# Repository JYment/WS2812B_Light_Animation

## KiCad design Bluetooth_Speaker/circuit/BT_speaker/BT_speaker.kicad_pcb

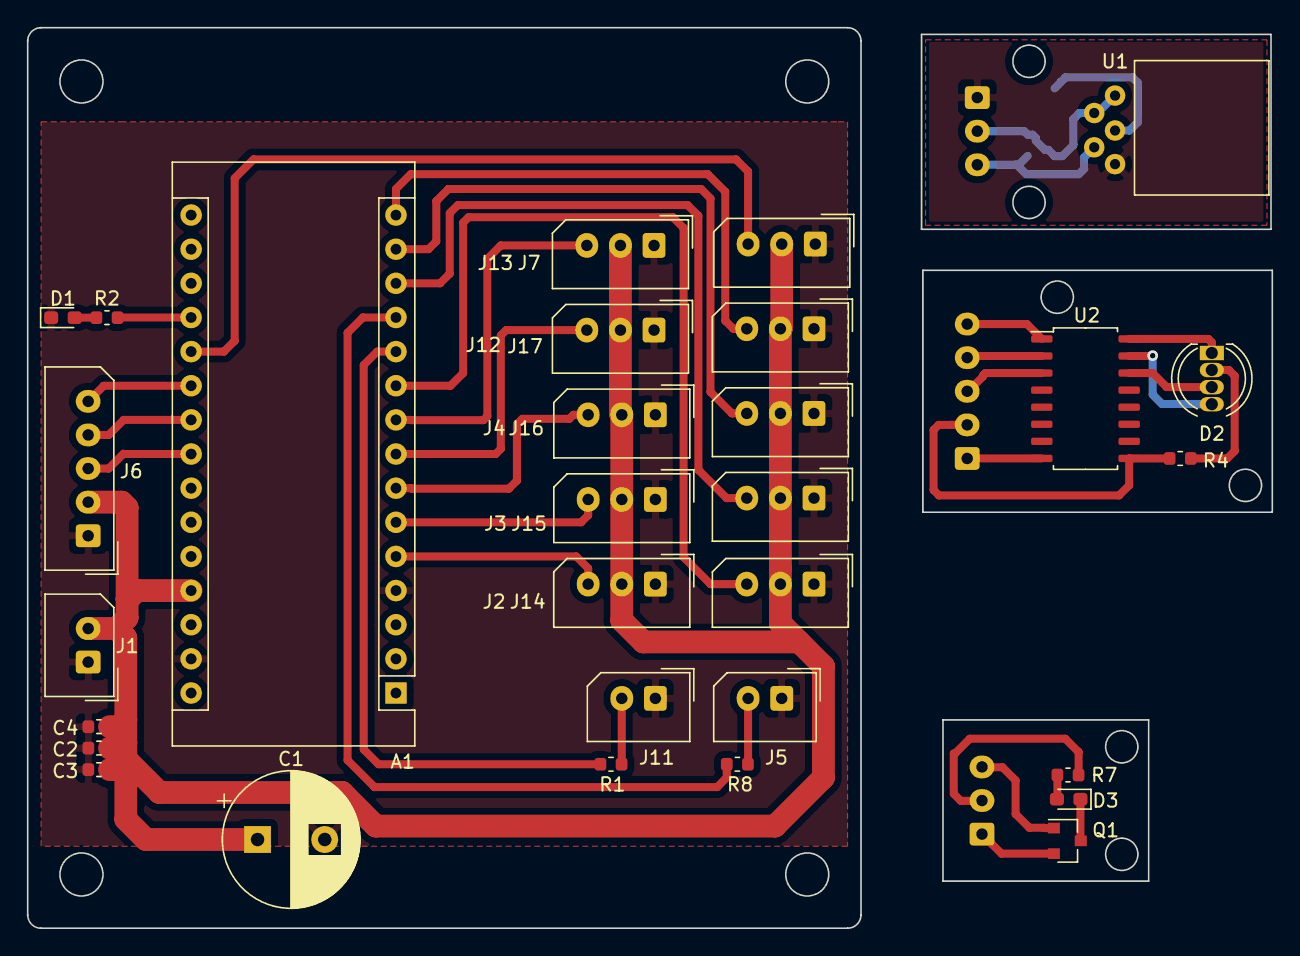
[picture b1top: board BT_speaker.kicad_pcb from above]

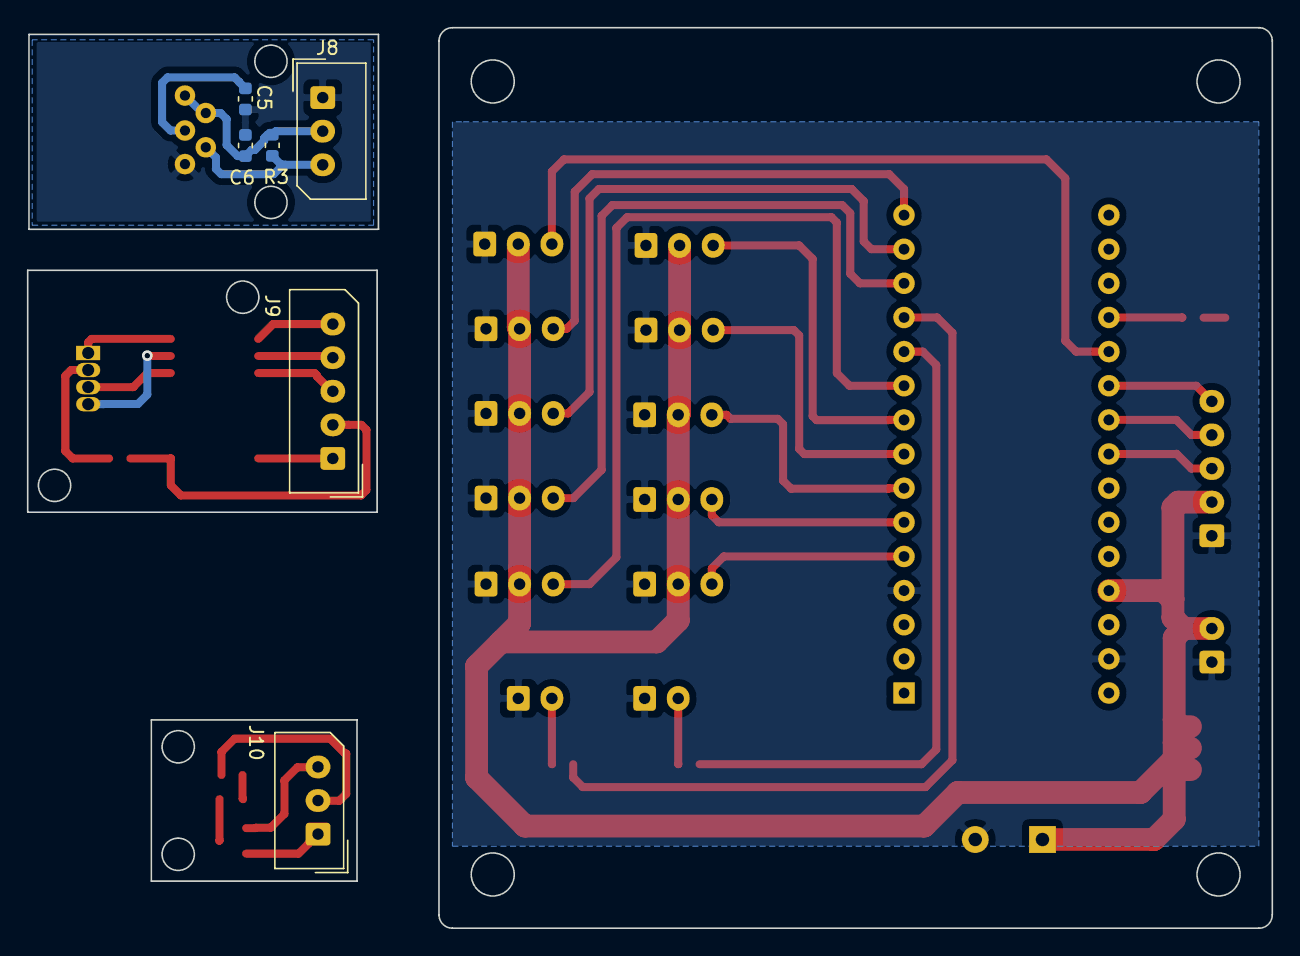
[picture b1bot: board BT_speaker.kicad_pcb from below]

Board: 2 copper layers, 92.6 x 67.0 mm, 36 parts (6 on the bottom side), 39 nets.

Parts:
A1: Arduino_Nano
C1: 220uF; CP_Radial_D10.0mm_P5.00mm
C2, C3, C4: 100nF; C_0603_1608Metric
C5, C6: 1uF; C_0603_1608Metric
D1: Blue; LED_0603_1608Metric_Pad1.05x0.95mm_HandSolder
D2: LED_RABG; LED_D5.0mm-4_RGB
D3: LED; LED_0603_1608Metric_Pad1.05x0.95mm_HandSolder
J1: POWER; Molex_SPOX_5267-02A_1x02_P2.50mm_Vertical
J2, J3, J4: TOUCH; Molex_SPOX_5267-03A_1x03_P2.50mm_Vertical
J5, J11: WS2812B; Molex_SPOX_5267-02A_1x02_P2.50mm_Vertical
J6, J9: Conn_01x05_Female; Molex_SPOX_5267-05A_1x05_P2.50mm_Vertical
J7: BLUE_LED; Molex_SPOX_5267-03A_1x03_P2.50mm_Vertical
J8, J10: Conn_01x03_Female; Molex_SPOX_5267-03A_1x03_P2.50mm_Vertical
J12: EX1; Molex_SPOX_5267-03A_1x03_P2.50mm_Vertical
J13: EX2; Molex_SPOX_5267-03A_1x03_P2.50mm_Vertical
J14: EX3; Molex_SPOX_5267-03A_1x03_P2.50mm_Vertical
J15: EX4; Molex_SPOX_5267-03A_1x03_P2.50mm_Vertical
J16: EX5; Molex_SPOX_5267-03A_1x03_P2.50mm_Vertical
J17: EX6; Molex_SPOX_5267-03A_1x03_P2.50mm_Vertical
Q1: 2N2222; SOT-23
R1, R8: 300; R_0603_1608Metric
R2, R4, R7: 470; R_0603_1608Metric
R3: 10k; R_0603_1608Metric
U1: TS01S_DIP; DS01S_DIP_SiliconType
U2: ULN2003; SOIC-16_4.55x10.3mm_P1.27mm

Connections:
+5V: A1.27, C1.1, C2.1, C3.1, C4.1, J1.2, J2.2, J3.2, J4.2, J6.2, J7.2, J12.2, J13.2, J14.2, J15.2, J16.2, J17.2
+5VD: J9.2, R4.1, U2.9
B_OUT: J9.5, U2.1
GND: A1.4, A1.29, C1.2, C2.2, C3.2, C4.2, D1.1, J1.1, J2.1, J3.1, J4.1, J5.1, J6.1, J7.1, J11.1, J12.1, J13.1, J14.1, J15.1, J16.1, J17.1
GNDA: J9.1, U2.8
GNDD: J10.1, Q1.2
GNDS: C5.1, C6.1, J8.1, U1.5
G_OUT: J9.4, U2.2
M_B_OUT: A1.21, J6.5
M_G_OUT: A1.22, J6.4
M_LED_BLUE: A1.20, J7.3
M_R_OUT: A1.23, J6.3
unnamed: A1.11, R1.1
unnamed: A1.12, R8.1
unnamed: A1.19, R2.2
unnamed: C5.2, U1.3
unnamed: D1.2, R2.1
unnamed: D2.1, U2.16
unnamed: D2.2, R4.2
unnamed: D2.3, U2.14
unnamed: D2.4, U2.15
unnamed: D3.1, Q1.3
unnamed: D3.2, R7.2
OUT: J8.3, R3.1, U1.4
PB0: J11.2, R1.2
PB1: J5.2, R8.2
PB2: A1.13, J15.3
PB3: A1.14, J16.3
PB4: A1.15, J17.3
PD2: A1.5, J2.3
PD3: A1.6, J3.3
PD4: A1.7, J4.3
PD5: A1.8, J12.3
PD6: A1.9, J13.3
PD7: A1.10, J14.3
R_OUT: J9.3, U2.3
SIG: J10.3, Q1.1
VDD: J10.2, R7.1
VDDF: C6.2, J8.2, R3.2, U1.1, U1.2

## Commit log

2019-12-17 Finish
